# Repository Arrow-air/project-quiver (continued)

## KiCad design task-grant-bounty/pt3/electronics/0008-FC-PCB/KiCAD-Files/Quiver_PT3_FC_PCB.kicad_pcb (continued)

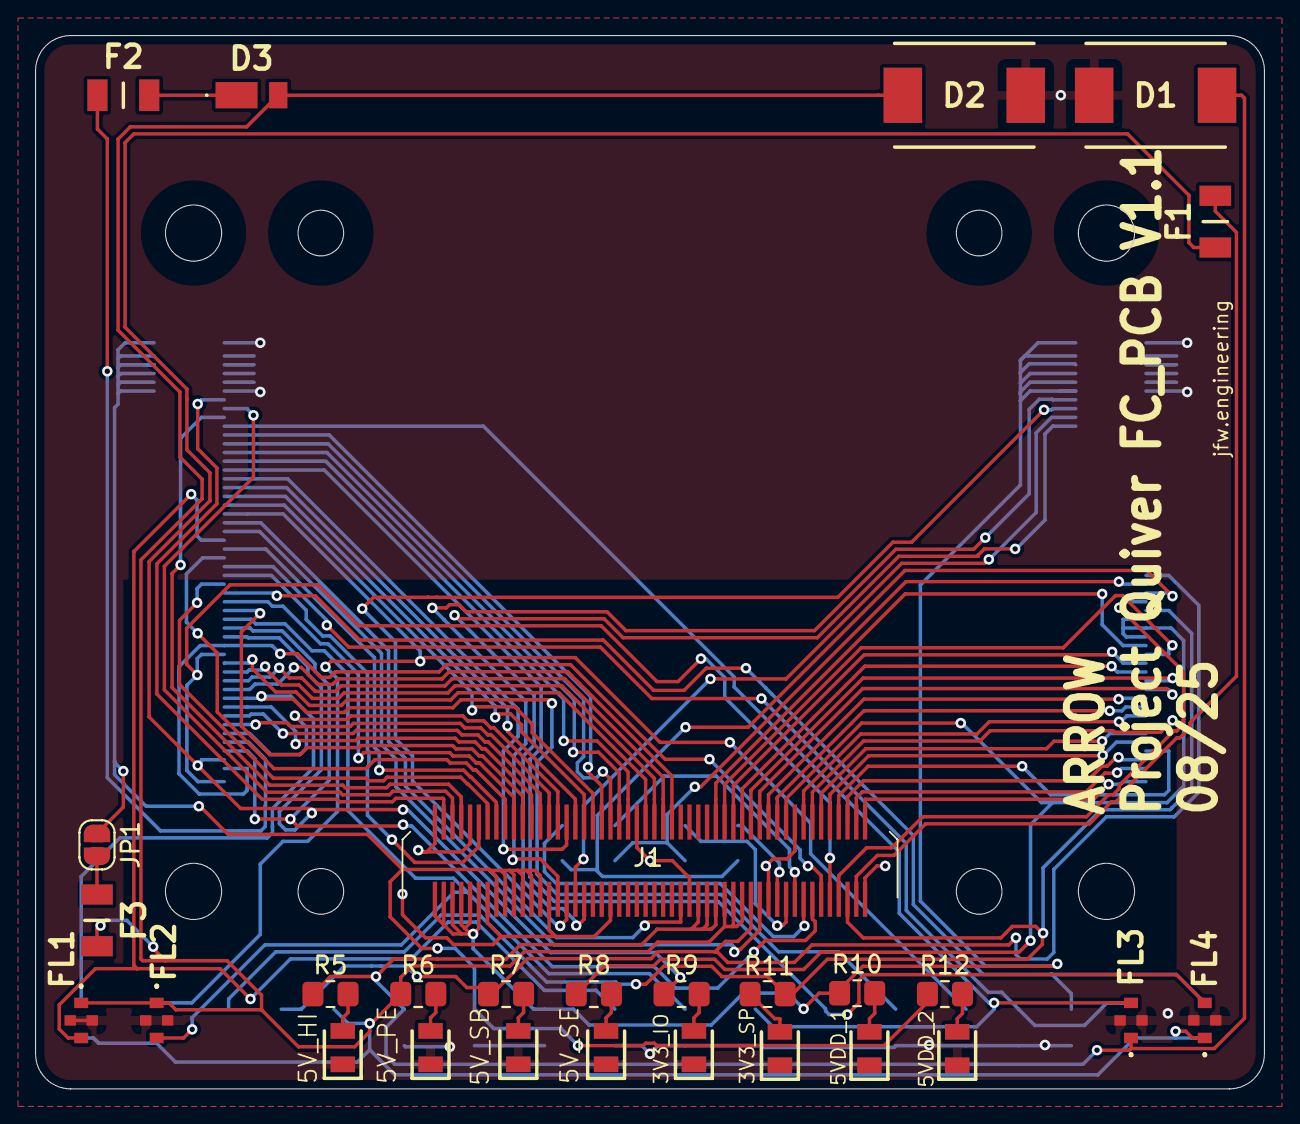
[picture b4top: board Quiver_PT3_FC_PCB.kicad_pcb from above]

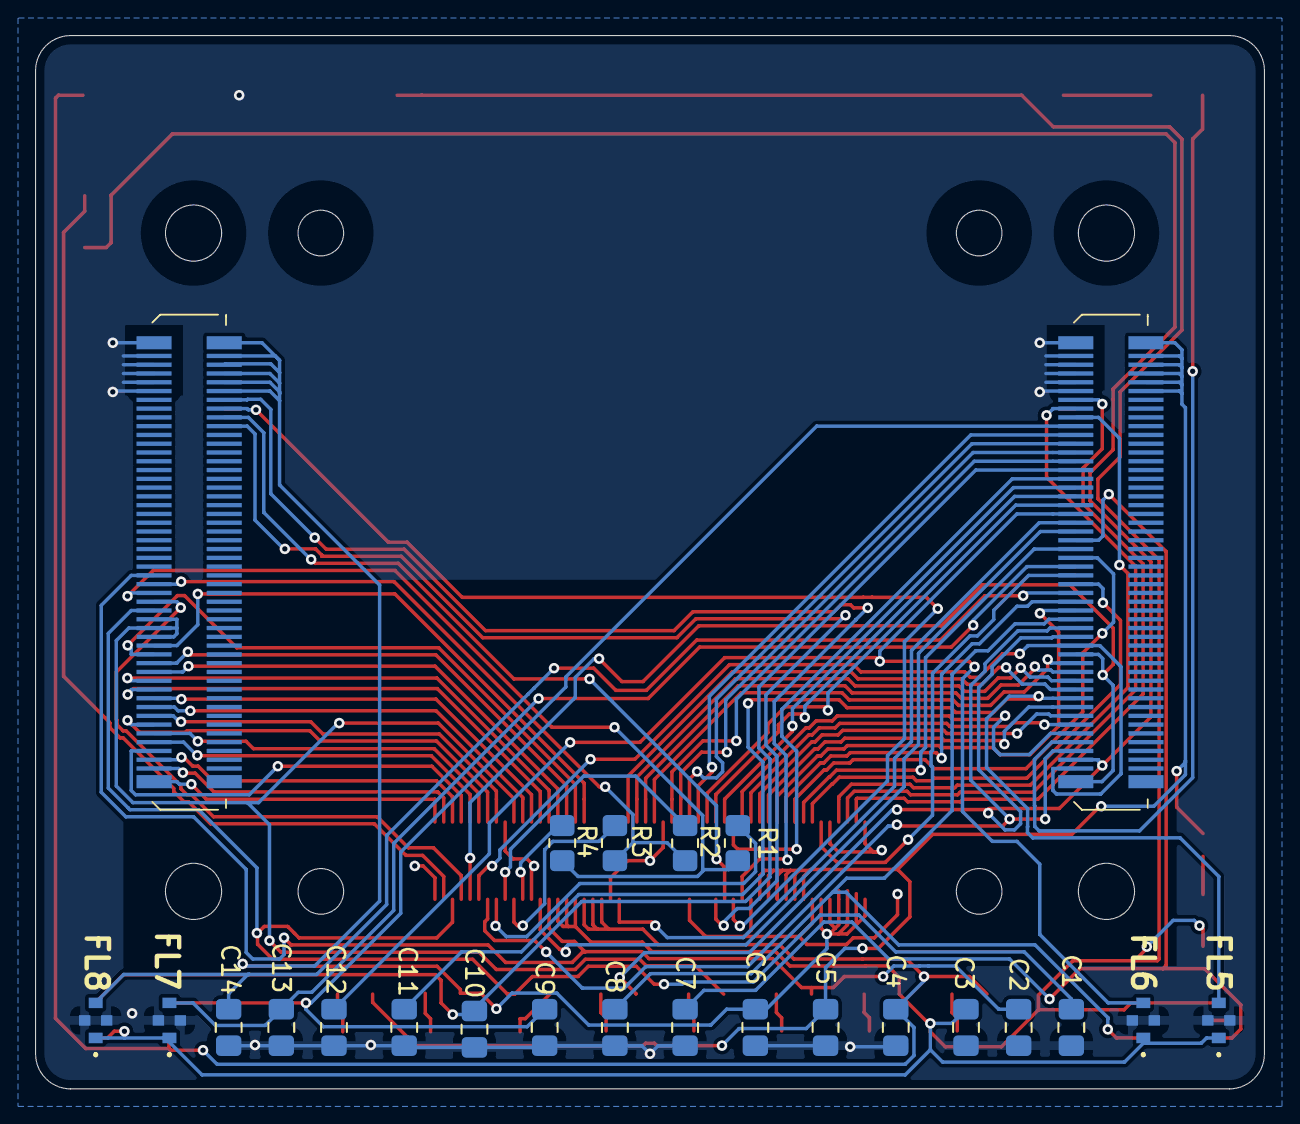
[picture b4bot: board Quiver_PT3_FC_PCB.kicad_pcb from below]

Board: 4 copper layers, 70.0 x 60.0 mm, 52 parts (24 on the bottom side), 86 nets.

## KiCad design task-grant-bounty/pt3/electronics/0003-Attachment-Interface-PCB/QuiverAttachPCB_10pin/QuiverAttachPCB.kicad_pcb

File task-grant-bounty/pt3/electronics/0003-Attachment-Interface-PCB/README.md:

# Project Quiver Payload Attachment PCB

## Overview

The Project Quiver payload attachment PCB is a simple 2-layer board designed for quickly interfacing payloads with the main system. 
This board provides standardized connectivity and mounting options for various payload configurations.

## Design Features

- **2-layer PCB design** for cost-effective manufacturing
- **Dual 10-pin headers** for flexible connectivity options
- **4x M2 mounting holes** for secure mechanical attachment
- **Configurable gender orientation** - populate either male or female connectors as needed

## Hardware Specifications

### Connectors
- **2x 10-pin headers** (2.54mm pitch)
  - Header J3: Female/Flat receiver pin payload interface
  - Header J2: Male/pogo pin interface
  - **Population options:**
    - Install male headers for mating with female cables/boards
    - Install female headers for mating with male cables/boards
    - Populate only one header if single connection is sufficient

### Mechanical
- **Mounting:** 4x M2 threaded holes
- **Board dimensions:** 15.8mm height x 23.5mm width
- **Board thickness:** 1.2mm **(thinner than standard 1,6mm!)**
- **Material:** FR4

## Assembly Instructions

### Component Population

1. **Header Selection:**
   - Determine required mating configuration
   - Install either male or female 10-pin headers (or both if needed)
   - Ensure proper alignment and orientation

2. **Mounting:**
   - Use 4x M2 screws for mechanical attachment
   - Recommended torque: screwdriver tightening, do not use impact driver or drill
   - Ensure even mounting pressure across all four points

### Pinout

**10-Pin Headers (J2 & J3):**

| Pin | J3 Function | J2 Function |
|-----|-------------|-------------|
| 1   | ETH_RX+    | ETH_RX+    |
| 2   | 12VSW      | 12VSW      |
| 3   | ETH_RX-    | ETH_RX-    |
| 4   | GND        | GND        |
| 5   | ETH_TX+    | ETH_TX+    |
| 6   | +12V       | +12V       |
| 7   | ETH_TX-    | ETH_TX-    |
| 8   | FMU_CH1    | FMU_CH1    |
| 9   | CAN1_P     | CAN1_P     |
| 10  | CAN1_N     | CAN1_N     |

**12-Pin MOLEX Locking Connector (J1 - 2077601281):**

| Pin | Function   | Description |
|-----|------------|-------------|
| 1   | ETH_RX+    | Ethernet receive positive |
| 2   | 12VSW      | Switched 12V power |
| 3   | ETH_RX-    | Ethernet receive negative |
| 4   | 12VSW      | Switched 12V power |
| 5   | ETH_TX+    | Ethernet transmit positive |
| 6   | GND        | Ground reference |
| 7   | ETH_TX-    | Ethernet transmit negative |
| 8   | GND        | Ground reference |
| 9   | CAN1_N     | CAN bus negative |
| 10  | 12V        | Main 12V power supply |
| 11  | CAN1_P     | CAN bus positive |
| 12  | FMU_CH1    | Flight Management Unit Channel 1 |

**Signal Descriptions:**
- **ETH_RX+/ETH_RX-**: Ethernet receive differential pair
- **ETH_TX+/ETH_TX-**: Ethernet transmit differential pair  
- **12VSW**: Switched 12V power output
- **+12V**: Main 12V power supply
- **GND**: Ground reference
- **FMU_CH1**: Flight Management Unit Channel 1
- **CAN1_P/CAN1_N**: CAN bus differential pair
s for maximum flexibility. J1 provides the same signals with additional ground pins for enhanced signal integrity and current handling.*
*Note: J2 and J3 headers have identical pinout

## Usage

### Configuration Options

1. **Single Header Configuration:**
   - Populate only J1 or J2 as needed
   - Use for simple payload interfaces

2. **Dual Header Configuration:**
   - Populate both headers
   - Enables 2x pin connections for each pinout

### Installation

1. Select appropriate M2 screws for your mounting surface
2. Align PCB with mounting holes
3. Secure with 4x M2 screws
4. Connect payload cables to populated headers

## Design Files

- Schematic: `QuiverAttachPCB.kicad_sch`
- PCB Layout: `QuiverAttachPCB.kicad_pcb`
- Gerber files: `/gerbers/`
- BOM: `QuiverAttachPCB_BOM.csv`

## Revision History

| Version | Date | Changes |
|---------|------|---------|
| v1.0    | 2025-06-02 | Initial release |
| v1.2    | 2025-07-31 | Center Molex header, adjust edge dimensions |

## Support

For technical questions or issues, please contact kellan@arrowair.com.

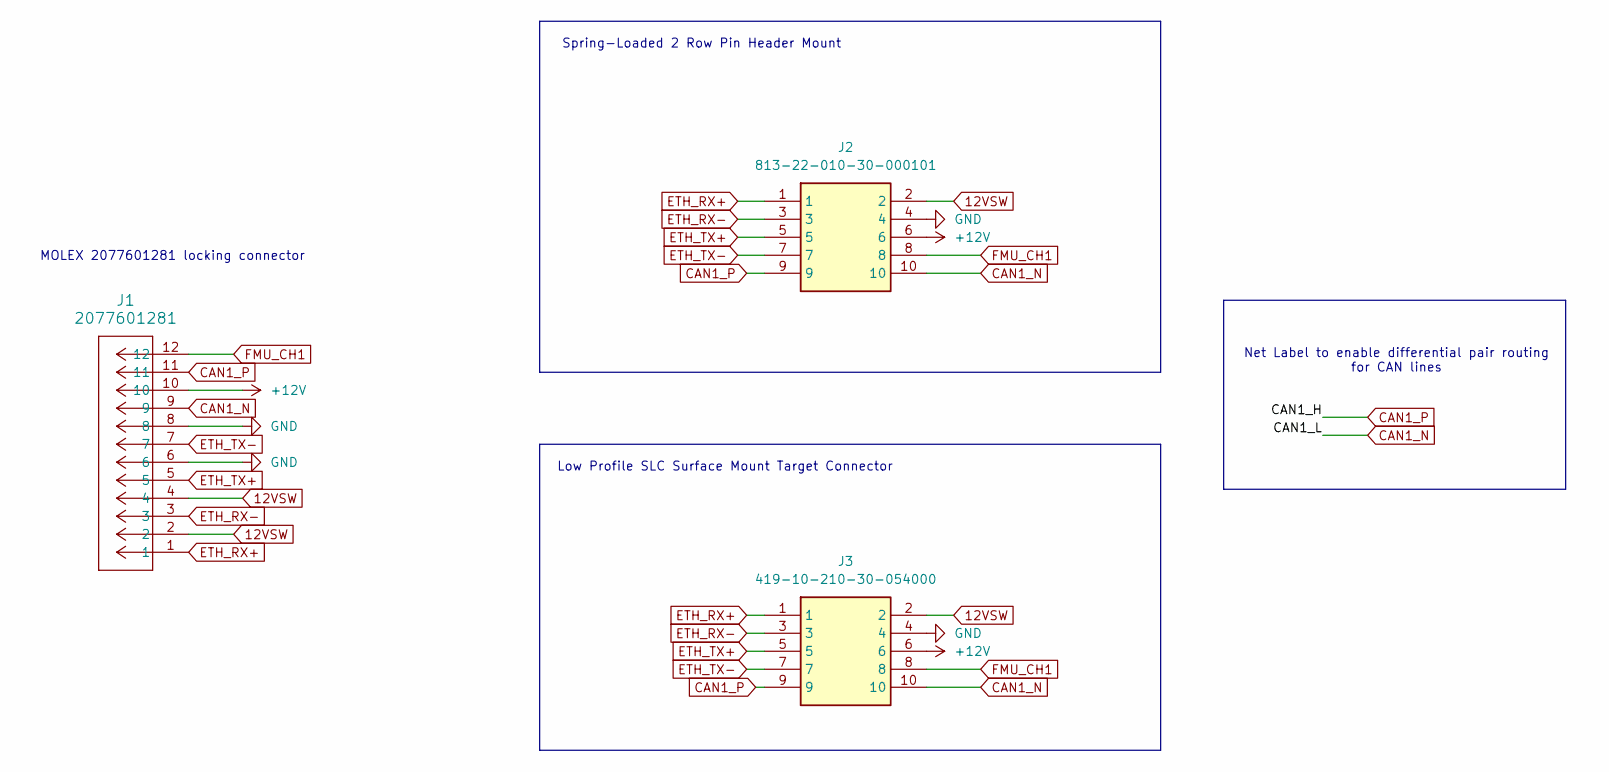
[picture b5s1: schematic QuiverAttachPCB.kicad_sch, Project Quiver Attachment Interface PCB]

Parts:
J1: 2077601281; CONN12_2077601281_MOL
J2: 813-22-010-30-000101; 8132201030000101; Mouser Part Number 575-8132201030000101
J3: 419-10-210-30-054000; Mouser Part Number 575-8132201030000101

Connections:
12VSW: J1.2, J1.4, J2.2, J3.2
+12V: J1.10, J2.6, J3.6
CAN1_N: J1.9, J2.10, J3.10
CAN1_P: J1.11, J2.9, J3.9
ETH_RX+: J1.1, J2.1, J3.1
ETH_RX-: J1.3, J2.3, J3.3
ETH_TX+: J1.5, J2.5, J3.5
ETH_TX-: J1.7, J2.7, J3.7
FMU_CH1: J1.12, J2.8, J3.8
GND: J1.6, J1.8, J2.4, J3.4

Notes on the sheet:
MOLEX 2077601281 locking connector
Spring-Loaded 2 Row Pin Header Mount
Low Profile SLC Surface Mount Target Connector
Net Label to enable differential pair routing for CAN lines

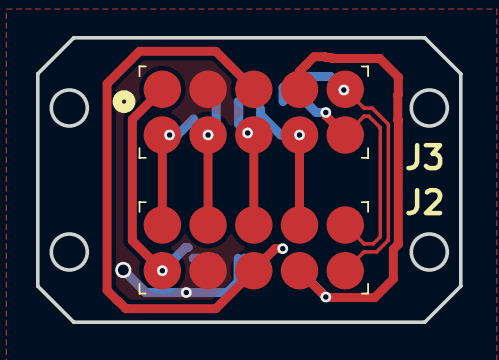
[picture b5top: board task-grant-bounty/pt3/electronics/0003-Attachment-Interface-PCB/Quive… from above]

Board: 2 copper layers, 23.5 x 15.8 mm, 3 parts (1 on the bottom side), 10 nets.

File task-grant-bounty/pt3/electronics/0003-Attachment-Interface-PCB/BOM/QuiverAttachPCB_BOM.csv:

QuiverAttachPCB
Id,Designator,Footprint,Quantity,Designation,Supplier,MPN,Product URL
1,J2,8132201030000101,1,813-22-010-30-000101,Mill-Max,813-22-010-30-000101,https://www.mouser.com/ProductDetail/Mill-Max/813-22-010-30-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
2,J1,CONN12_2077601281_MOL,1,2077601281,Molex,2077601281,https://www.mouser.com/ProductDetail/Molex/207760-1281?qs=Ge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
3,J3,419-10-210-30-054000,1,419-10-210-30-054000,Mill-Max,419-10-210-30-054000,https://www.mouser.com/ProductDetail/Mill-Max/419-10-210-30-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
,Not Populated,204523-1201,1,204523-1201,Molex,204523-1201,https://www.mouser.com/ProductDetail/Molex/204523-1201?qs=Ge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

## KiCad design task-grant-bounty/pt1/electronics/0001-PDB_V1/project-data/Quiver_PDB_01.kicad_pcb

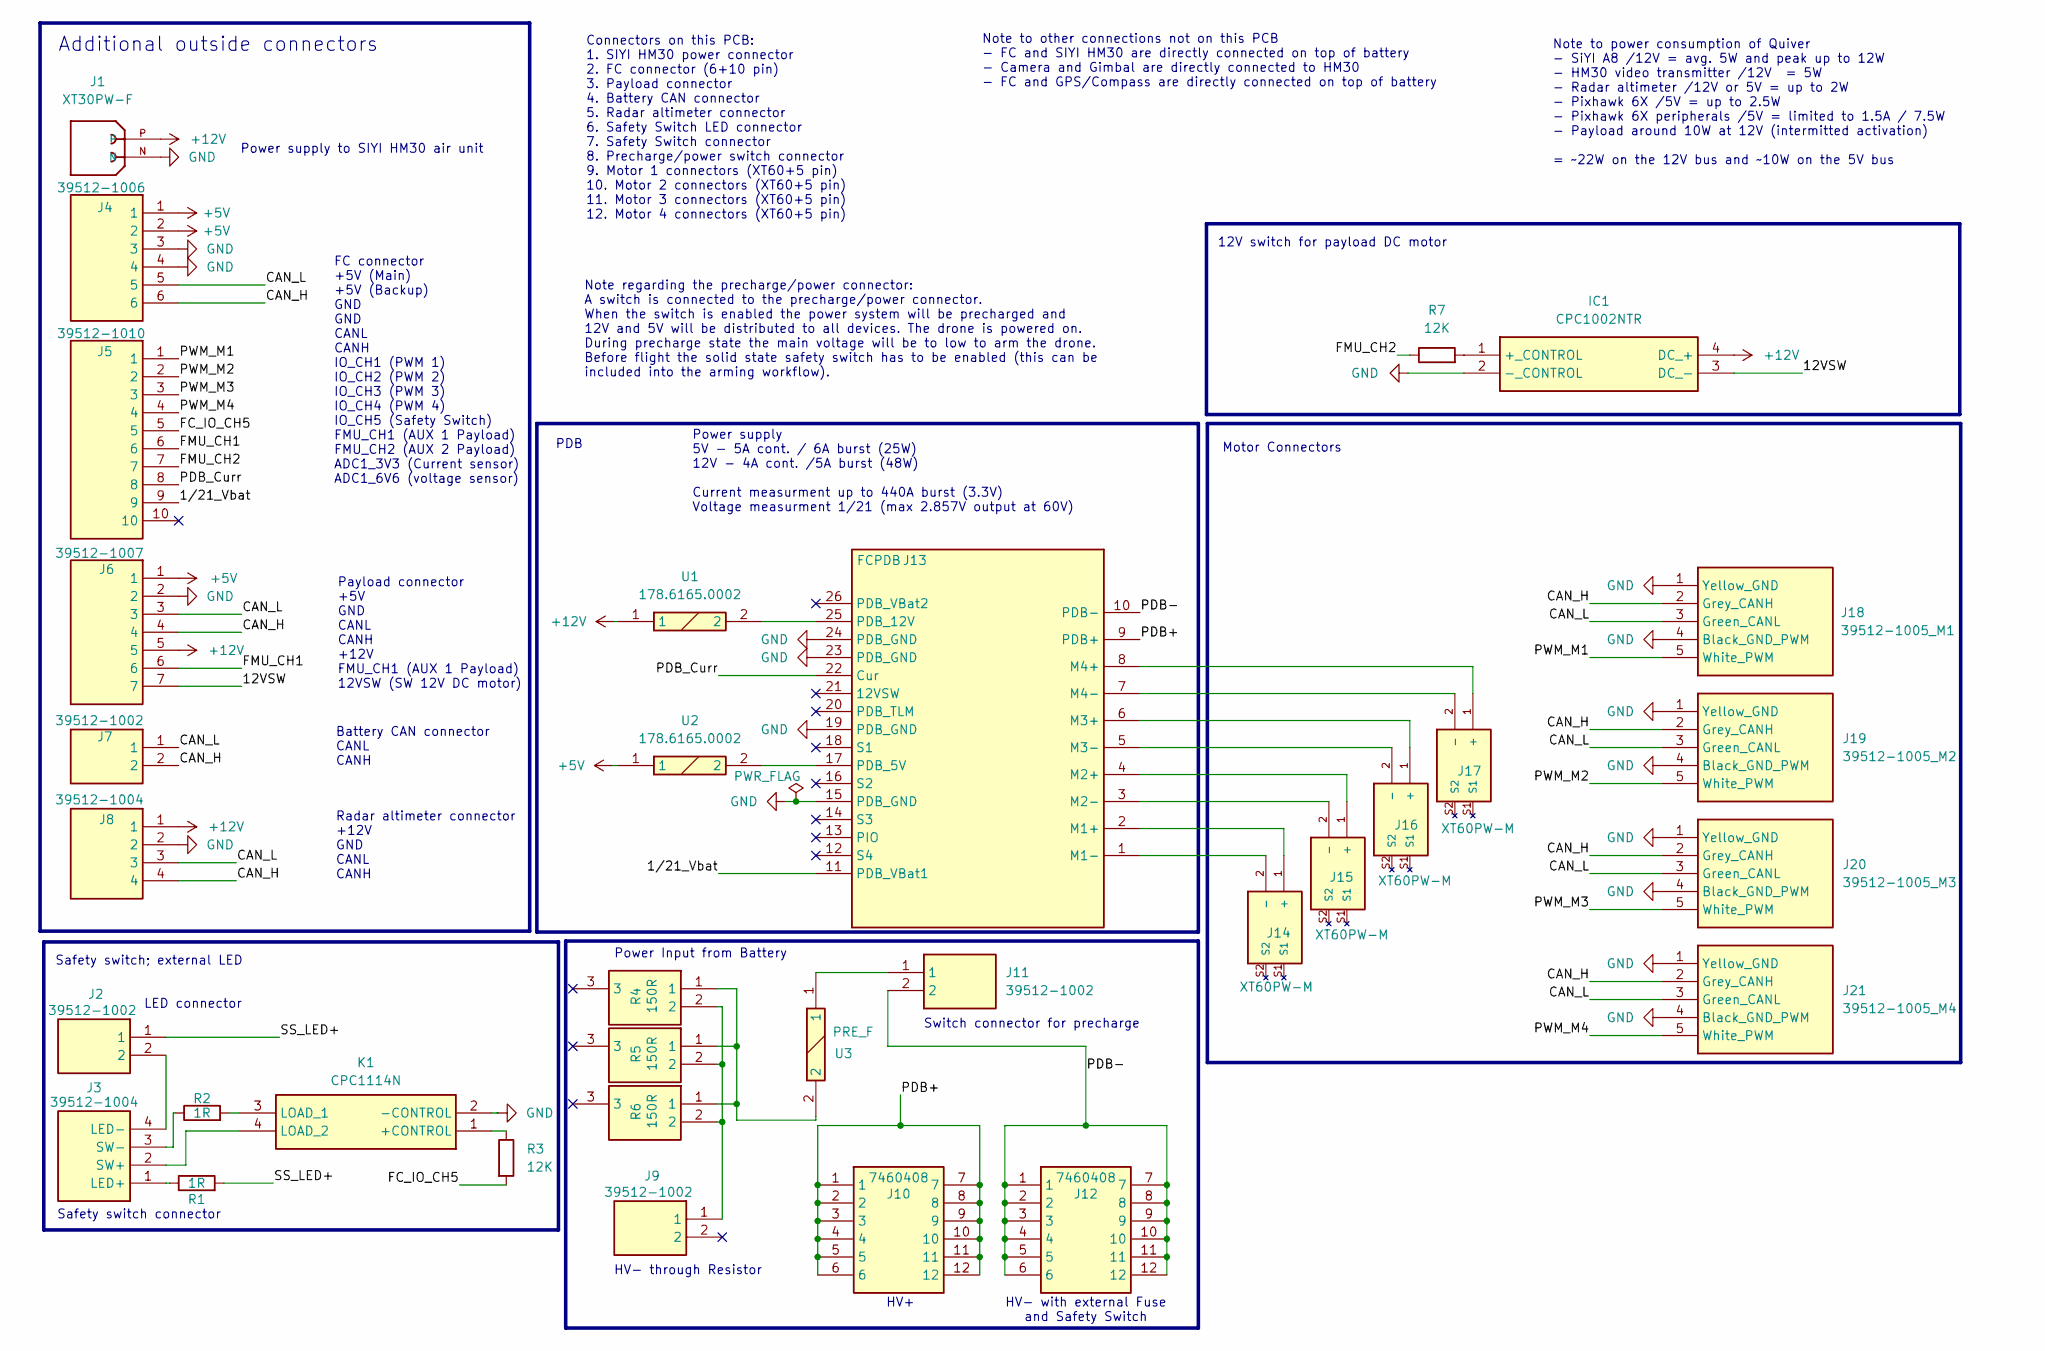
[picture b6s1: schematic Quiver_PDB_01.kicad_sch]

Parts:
IC1: CPC1002NTR; SOP254P610X216-4N; Mouser Part Number 849-CPC1002NTR
J1: XT30PW-F; XT30PW-F_AMASS_XT30PW-F; PARTREV 1.2
J2, J7, J9, J11: 39512-1002; SHDRRA2W80P0X381_1X2_901X920X730P; Mouser Part Number 538-39512-1002
J3, J8: 39512-1004; SHDRRA4W80P0X381_1X4_1663X920X730P; Mouser Part Number 538-39512-1004
J4: 39512-1006; 395121006; Mouser Part Number 538-39512-1005
J5: 39512-1010; 395121010; Mouser Part Number 538-39512-1005
J6: 39512-1007; 395121007; Mouser Part Number 538-39512-1005
J10, J12: 7460408; Mouser Part Number 710-7460408
J13: FCPDB; PDB_2; Mouser Part Number 200-SSQ12001FD
J14, J15, J16, J17: XT60PW-M; XT60PW-M_AMASS_XT60PW-M; PARTREV V1.2
J18: 39512-1005_M1; 395121005; Mouser Part Number 538-39512-1005
J19: 39512-1005_M2; 395121005; Mouser Part Number 538-39512-1005
J20: 39512-1005_M3; 395121005; Mouser Part Number 538-39512-1005
J21: 39512-1005_M4; 395121005; Mouser Part Number 538-39512-1005
K1: CPC1114N; SOP254P610X218-4N; Mouser Part Number 849-CPC1114N
R1, R2: 1R; R_0805_2012Metric_Pad1.20x1.40mm_HandSolder
R3, R7: 12K; R_0805_2012Metric_Pad1.20x1.40mm_HandSolder
R4, R5, R6: 150R; PWR163S2550R0F; Mouser Part Number 652-PWR163S-25-50R0F
U1, U2: 178.6165.0002; 17861650002; Mouser Part Number 576-178.6165.0002
U3: PRE_F; 17861650002; Mouser Part Number 576-178.6165.0002

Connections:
+5V: J4.1, J4.2, J6.1, U2.1
+12V: IC1.4 (DC_+), J1.P, J6.5, J8.1, U1.1
/1/21_Vbat: J5.9, J13.11 (PDB_VBat1)
/12VSW: IC1.3 (DC_-), J6.7
/CAN_H: J4.6, J6.4, J7.2, J8.4, J18.2 (Grey_CANH), J19.2 (Grey_CANH), J20.2 (Grey_CANH), J21.2 (Grey_CANH)
/CAN_L: J4.5, J6.3, J7.1, J8.3, J18.3 (Green_CANL), J19.3 (Green_CANL), J20.3 (Green_CANL), J21.3 (Green_CANL)
/FC_IO_CH5: J5.5, R3.2
/FMU_CH1: J5.6, J6.6
/FMU_CH2: J5.7, R7.1
/PDB+: J10.1, J10.2, J10.3, J10.4, J10.5, J10.6, J10.7, J10.8, J10.9, J10.10, J10.11, J10.12, J13.9 (PDB+)
/PDB-: J11.2, J12.1, J12.2, J12.3, J12.4, J12.5, J12.6, J12.7, J12.8, J12.9, J12.10, J12.11, J12.12, J13.10 (PDB-)
/PDB_Curr: J5.8, J13.22 (Cur)
/PWM_M1: J5.1, J18.5 (White_PWM)
/PWM_M2: J5.2, J19.5 (White_PWM)
/PWM_M3: J5.3, J20.5 (White_PWM)
/PWM_M4: J5.4, J21.5 (White_PWM)
/SS_LED+: J2.1, R1.2
GND: IC1.2 (-_CONTROL), J1.N, J4.3, J4.4, J6.2, J8.2, J13.15 (PDB_GND), J13.19 (PDB_GND), J13.23 (PDB_GND), J13.24 (PDB_GND), J18.1 (Yellow_GND), J18.4 (Black_GND_PWM), J19.1 (Yellow_GND), J19.4 (Black_GND_PWM), J20.1 (Yellow_GND), J20.4 (Black_GND_PWM), J21.1 (Yellow_GND), J21.4 (Black_GND_PWM), K1.2 (-CONTROL)
unnamed: IC1.1 (+_CONTROL), R7.2
unnamed: J3.1 (LED+), R1.1
unnamed: J2.2, J3.4 (LED-)
unnamed: J3.2 (SW+), K1.4 (LOAD_2)
unnamed: J3.3 (SW-), R2.1
unnamed: J9.1, R4.2, R5.2, R6.2
unnamed: J11.1, U3.1
unnamed: J13.2 (M1+), J14.1 (+)
unnamed: J13.1 (M1-), J14.2 (-)
unnamed: J13.4 (M2+), J15.1 (+)
unnamed: J13.3 (M2-), J15.2 (-)
unnamed: J13.6 (M3+), J16.1 (+)
unnamed: J13.5 (M3-), J16.2 (-)
unnamed: J13.8 (M4+), J17.1 (+)
unnamed: J13.7 (M4-), J17.2 (-)
unnamed: J13.17 (PDB_5V), U2.2
unnamed: J13.25 (PDB_12V), U1.2
unnamed: K1.1 (+CONTROL), R3.1
unnamed: K1.3 (LOAD_1), R2.2
unnamed: R4.1, R5.1, R6.1, U3.2

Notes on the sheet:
HV- with external Fuse and Safety Switch
HV+
HV- through Resistor
FC connector +5V (Main) +5V (Backup) GND GND CANL CANH IO_CH1 (PWM 1) IO_CH2 (PWM 2) IO_CH3 (PWM 3) IO_CH4 (PWM 4) IO_CH5 (Safety Switch) FMU_CH1 (AUX 1 Payload) FMU_CH2 (AUX 2 Payload) ADC1_3V3 (Current sensor) ADC1_6V6 (voltage sensor)
PDB
12V switch for payload DC motor
Power supply 5V - 5A cont. / 6A burst (25W) 12V - 4A cont. /5A burst (48W) Current measurment up to 440A burst (3.3V) Voltage measurment 1/21 (max 2.857V output at 60V)
Radar altimeter connector +12V GND CANL CANH
Power supply to SIYI HM30 air unit
Power Input from Battery
Motor Connectors
Switch connector for precharge
Battery CAN connector CANL CANH
Additional outside connectors
LED connector
Safety switch connector
Safety switch; external LED
Note to other connections not on this PCB - FC and SIYI HM30 are directly connected on top of battery - Camera and Gimbal are directly connected to HM30 - FC and GPS/Compass are directly connected on top of battery
Connectors on this PCB: 1. SIYI HM30 power connector 2. FC connector (6+10 pin) 3. Payload connector 4. Battery CAN connector 5. Radar altimeter connector 6. Safety Switch LED connector 7. Safety Switch connector 8. Precharge/power switch connector 9. Motor 1 connectors (XT60+5 pin) 10. Motor 2 con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
Note regarding the precharge/power connector: A switch is connected to the precharge/power connector. When the switch is enabled the power system will be precharged and 12V and 5V will be distributed to all devices. The drone is powered on. During precharge state the main voltage will be to low to 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
Note to power consumption of Quiver - SiYI A8 /12V = avg. 5W and peak up to 12W - HM30 video transmitter /12V = 5W - Radar altimeter /12V or 5V = up to 2W - Pixhawk 6X /5V = up to 2.5W - Pixhawk 6X peripherals /5V = limited to 1.5A / 7.5W - Payload around 10W at 12V (intermitted activation) = ~22W 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
Payload connector +5V GND CANL CANH +12V FMU_CH1 (AUX 1 Payload) 12VSW (SW 12V DC motor)

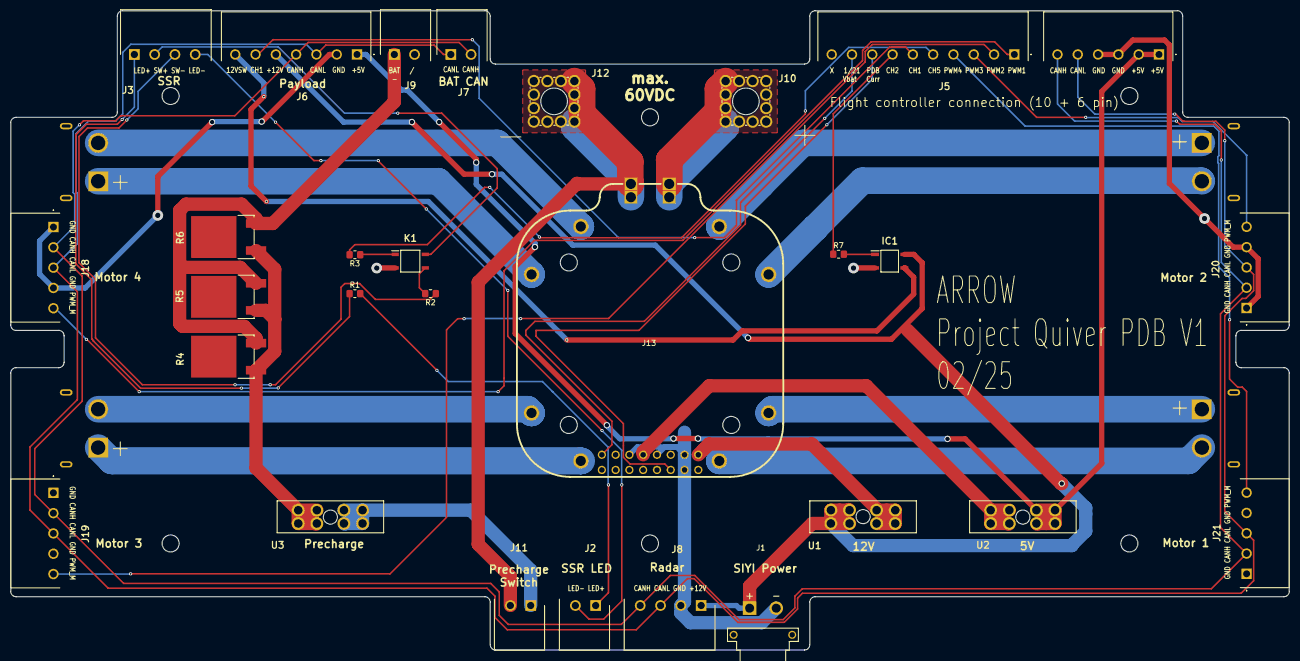
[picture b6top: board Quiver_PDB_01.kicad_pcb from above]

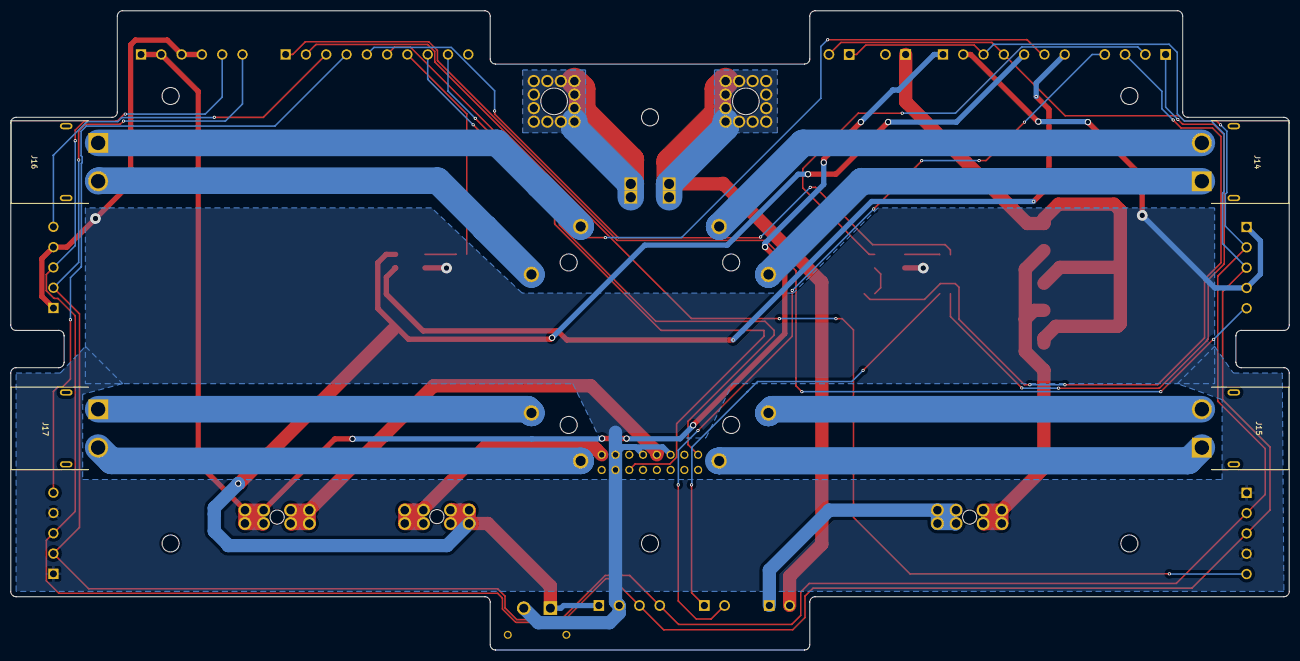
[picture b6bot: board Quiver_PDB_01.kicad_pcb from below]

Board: 2 copper layers, 240.0 x 120.0 mm, 33 parts (4 on the bottom side), 38 nets.

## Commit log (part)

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2026-02-25 adjusted folder structure
2026-02-25 information note format
2026-02-25 replacement log
2026-02-25 image folder
2026-02-25 placeholders
2026-02-26 docs: add nail board diagrams for all 28 harnesses (HAR-001 through HAR-028)
    - Add flat nail board PNGs for all harnesses with connector designators,
    pin assignments, wire colors/gauges, and BOM-derived cut lengths
    - Replace all [Image Placeholder] tags in Harness-Manufacturing-Guide.md
    - Grouped sections (HAR-004-007, HAR-008-011, HAR-012-013, HAR-019-020,
    HAR-021-022, HAR-023-025) show individual nail boards for each harness
    Generated by Vector from 4020_dev_kit.step geometry + harnessing guide data.
2026-02-26 docs: add cut lengths to Section 3 tables for all harnesses
    - HAR-0017: replace xxmm placeholder with 485 mm (BOM-derived)
    - HAR-0016: replace N/A with required cable length table (195 mm)
    - HAR-0019/020: replace N/A with JST-GH required lengths (170/160 mm)
    - HAR-0021/022: replace N/A with JST-GH required lengths (205/70 mm)
    - HAR-0023/024/025: replace N/A with JST-GH required lengths (120/205/155 mm)
    - HAR-0026: replace N/A with JST-GH required length (65 mm)
2026-02-26 Vector's update
2026-02-26 notation updated
2026-02-27 docs: Add OpenDroneID support (DroneBeacon db201) + updated firmware
    - arducopter-pixhawk6c.apj: rebuilt with AP_OPENDRONEID_ENABLED=1 (1,617 KB, 302 KB headroom)
    Standard Pixhawk 6C bootloader unchanged — firmware can still be updated freely.
    - parameters/params-remoteid.param: minimal param set to enable db201 via DroneCAN
    (DID_ENABLE, DID_CANDRIVER=1, DID_MAVPORT=-1)
    - docs/firmware/README.md: updated to document OpenDroneID support and param load order
2026-02-27 fix: Correct .apj firmware image encoding (zlib+base64, not raw base64)
    The previously generated .apj used raw base64-encoded binary, but ArduPilot's
    uploader expects zlib-compressed then base64-encoded image data. This caused
    Mission Planner to report 'Firmware file has 0 length image' when flashing.
    Fixed: compress with zlib.compress() before base64 encoding.
2026-03-03 feat: Add improved Tattu BMS DroneCAN bridge
    Fixes spurious SOC=0% readings with three changes:
    1. Drain full frame burst before DroneCAN spin:
    Original processed one frame per loop iteration, causing frame drops
    when the Tattu burst arrived faster than the loop ran.
    2. SOC/voltage sanity validation:
    Rejects out-of-range decodes (voltage outside 14S bounds, SOC > 100%)
2026-03-03 fix: Relax frame length validation — final Tattu frame is 6 bytes
    Frame 7 (the last frame) legitimately contains only 6 bytes in the Tattu
    protocol. The strict 'all frames >= 7 bytes' check was discarding every
    sequence. Now only frame 0 has a hard minimum; all other frames use
    min(len, 7) for reassembly.
2026-03-03 fix: db201 goes on CAN2, not CAN1 — CAN1 saturated by ESCs
    CAN1 is too busy with ESC traffic for db201 node ID enumeration to succeed.
    CAN2 at 1Mbps works reliably. Updated:
    - DID_CANDRIVER: 1 → 2
    - CAN_P2_BITRATE: set to 1000000 (overrides standard-params 500kbps)
2026-03-03 fix: db201 on CAN2 at 500kbps (shared with nanoradar)
    Remove CAN_P2_BITRATE override — CAN2 must stay at 500kbps for nanoradar.
    db201 CAN bitrate must be changed to 500kbps via DroneBeacon Bluetooth app
    before it will enumerate on CAN2.
2026-03-10 Rename task-grant-bounty/Dev-Kit/images/Quiver Payload Network.png to task-grant-bounty/Dev-Kit/images/payload/Quiver Payload Network.png
2026-03-10 Remove upload date from developer guide
    Removed upload date from the Quiver SDK Developer Guide.
2026-03-10 FIX formatting errors in last commit
2026-03-10 FIX folder error + UPDATE title for previous commit
2026-03-11 Hub/SDK Updates
2026-03-11 Enclosure Updates
2026-03-11 FIX format for previous commit
2026-03-11 Adjust Link and pictures
2026-03-11 jpg JPG
2026-03-11 Update vibration mount and weight reduction information noteand
2026-03-12 colon
2026-03-12 spacing
2026-03-18 hi alperen
2026-03-18 bye alperen
2026-03-23 Updated "warning" blockquote
2026-03-23 formatting and contnet updates
2026-03-23 Manufacturing guide updates
2026-03-23 PCB manuals added to Manufacturing guide
2026-03-23 Revise Quiver SDK Test information and references
    Updated revision history and reference notes for clarity.
2026-03-26 UPDATE pilot-handbook for "gimbal camera" + multiple "failure" + "contact" parts
2026-03-30 Update Pilot-Handbook.md
    Safety-Critical Gaps
    2. §3.3 Step 9 / §2.5.3 — Replace "adequate GPS fix" with a specific threshold.
2026-04-10 fix: db201 confirmed working on CAN1; update params from flight testing
    params-remoteid.param:
    - DID_CANDRIVER: 2 → 1 (CAN1 confirmed working with ESCs)
    - Added DID_BARO_ACC=-1
    - Removed CAN2/500kbps workaround notes
    standard-params.param:
    - GPS_HDOP_GOOD: 140 → 160
2026-04-14 docs: add Quiver PT1 bill of materials
    - Markdown page formatted for Docusaurus with categorized tables
    - CSV source file for programmatic access
    - Sourced from the PT1 BOM Google Sheet
    - Links to suppliers, specs, and quantities for all components
    - Cost summary: ~$6,970 per build
2026-04-15 Relocate structural assembly guide and assets
    Move General-Assembly-Guide contents up to Assembly-Guides and regroup assets under assets/images/structural and assets/models/structural. Update image and CAD references in structural-assembly.md.
2026-04-15 Update asset paths in structural assembly guide
    Point image and CAD links to assets/images/structural and assets/models/structural after the asset relocation.
2026-04-15 Revise Dev-Kit Engineering Report with updates
    Updated the Dev-Kit Engineering Report with new sections on structural improvements, electronics integration, software upgrades, and performance metrics. Adjusted sidebar position and added detailed 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
2026-04-15 Add missing step13_1 image for structural assembly guide
2026-04-15 fix: add missing images referenced by assembly and manufacturing docs
    - Copy step13_1.png to structural assembly assets (was only in pt3-assembly-guides)
    - Copy 1221_1222.png and .step to Dev-Kit-Guides/assets (Manufacturing-Guide references)
2026-04-15 fix: replace broken image refs with TODO placeholders
    Images differ between PT3 and devkit, so using PT3 assets would be
    incorrect. Replaced with TODO notes until correct devkit images are available.
    Affected files:
    - structural-assembly.md: step13_1.png (busbar installation)
    - Manufacturing-Guide.md: 1221_1222.png and .step (battery wall)
2026-04-16 Add transport case foam insert information note
    Add Pelican 1640 custom foam insert documentation for the Quiver
    transport case bounty (Issue #192). Includes:
    - Information note with foam layer design, CAD links, manufacturing
    process, material list, and assembly instructions
    - 5 reference images (2 CAD renders, 3 build photos)
    - 2 DXF laser cutting layouts (Foam_1.dxf, Foam_2.dxf)
2026-04-16 Update structural assembly guide (BOM, HTML images, step shift)
    - Move tool list into BOM as Table 3 (Tools and Consumables) with McMaster refs for Loctite 222/242 and Würth Super RTV Silicone
    - Remove silicone adhesive between aluminum layer references and delete the four contact images (step1_3, step2_3, step4_3, step5_3)
    - Convert all image references to HTML img tags with width="600"
    - Shift Steps 19-21 to Steps 20-22 and rename associated assets to free the Step 19 slot
    - Populate Step 20 (Main Enclosure and Top Cap) parts list including consumables
    - Replace step16_1.png with upscaled version
2026-04-17 Fix landing legs wording, remove bounty proposal section
    - Change 'minus detached landing legs' to 'with detached landing legs'
    - Remove Bounty or Grant Proposal Document section (no formal bounty
    proposal exists for this work)
2026-04-17 Revise structural assembly guide: fastener corrections, consumables, wording
    - Fix BOM quantities to match step usage across all fasteners
    - Remove unused Screw 3 (old) and Insert 3 (old), renumber Screw 18 and Insert 5 into the freed slots
    - Add consumables (Loctite, Würth RTV, double-sided tape, silicone foam seal strip) to Parts needed in all steps that use them
    - Normalize parenthetical fastener descriptions to match BOM exactly
    - Fix grammar: "shown to" -> "shown in", "connecters" -> "connectors", consistent "DO NOT use" casing
    - Fix Step 14 fastener type (Screw 5 vs Screw 7) and Step 13 missing Loctite in parts list
2026-04-18 fix: sync Manufacturing-Guide with structural-assembly v1.1 changes
    Alperen's PR #195 reorganized structural-assembly.md, removing the
    'Adhesive Area' column and consolidating steps to 2 images each.
    Manufacturing-Guide.md still had the old 3-column tables referencing
    deleted images (step1_3, step2_3, step4_3, step5_3, step9_6).
    Updated tables to match the current 2-column structure rather than
    leaving TODO placeholders.
2026-04-20 docs: sync BOM with Google Sheet updates
    - Add 134X: aluminum landing gear tube joints (INNLOI) replacing 3D-printed T-adapters
    - Add 3231: power switch (Digikey)
    - Update CF tube dimensions from 30x26 to 30x28mm
    - Update total estimate to ~$7,023
2026-04-20 docs: major BOM update from Alperen's manufacturing guide alignment
    - Remove old fastener section (0023-0040) — replaced by detailed 51XX series
    - Add all 3D-printed parts (21X1, 2131, 221X, 2311-2341, 2411-2412)
    - Add new equipment: PPP adapter (3271), busbars (3322/3323), power switch (3231)
    - Renumber: shock absorber → 135X, Remote ID → 3261
    - Add complete Misc section (5XXX): rivets, screws, inserts, washers, grommets, seals, vibration mounts, tools, adhesives
    - Update 133X supplier link to RJXHobby
2026-04-20 Update PPP Adapter part number in assembly guide
2026-04-20 docs: add hyperlinks to all McMaster P/Ns and Amazon items in Misc section
2026-04-20 docs: add exact Amazon links for misc hardware (5132-5135)
2026-04-21 Update step3_3 threadlocker application image
2026-04-21 Add Loctite Red 262 for motor arm connector fasteners
    - Add Loctite Threadlocker Red 262 (high-strength) to Tools and Consumables table with McMaster reference
    - Step 3: use Red 262 on the permanent motor arm connector fasteners; Blue 242 stays for the connector-to-chassis screws
    - Step 21: explicitly call out Loctite Purple 222 application for antennas (small amount on base threads) and push button
2026-04-21 Restructure General Assembly section with updated BOM and steps
2026-04-22 fix: Correct .apj magic string (APFWv1 → APJFWv1)
    Our hand-generated .apj used 'APFWv1' but ArduPilot's standard is 'APJFWv1'.
    The OTA service's apj→abin converter checks for this magic and would reject
    our custom .apj files.
2026-04-30 docs: update pilot handbook relay startup guidance
2026-04-30 ci: ignore generated hardware artifacts in sanity checks
2026-04-30 docs: add SSR verification fallback
2026-04-30 docs: clarify SSR verification without Tattu bridge
2026-04-30 Adding Archive folder to Guides
2026-05-01 docs: remove ADR and meeting templates
2026-05-05 Fix archived SDK guide image path
2026-05-06 docs: include updated devkit engineering report draft
2026-05-11 Reorder Screw 3 to correct numerical position in fasteners BOM
2026-05-12 docs: localize dev kit report images
2026-05-12 Update NRA15 and camera bolt sizes per assembly feedback
2026-05-13 docs: reorganize Quiver documentation IA
    Group current Quiver docs by audience and workflow, archive legacy PT3 assembly material, and clean up sidebar labels/order for the Docusaurus import.
2026-05-13 docs: update bottom payload harness instructions
2026-05-13 docs: add HAR-014 complete harness reference photo
2026-05-13 docs: fix HAR-014 reference photo rendering
2026-05-14 docs: dedupe manufacturing and harness guides
2026-05-15 docs: normalize harness IDs in tables
2026-05-15 docs: rename canonical Quiver BOM
2026-05-15 docs: sync BOM from Google Sheet
2026-05-20 docs: add PWM MAD 4x08 parameter variant
2026-05-29 Added fusion link to project readme and manufacturing guide
2026-06-10 Revert "fixup! ci: terraform provisioned file changes"
    This reverts commit 0f2abc5e3766a2f459a777524694517443e961b1.
2026-06-11 fix: restore repo-specific cspell ignore paths
    The June 7 Terraform repository sync overwrote this file with the
    shared org template, dropping the KiCad/hardware binary ignore paths
    added in #219. Terraform no longer manages this file's content
    (Arrow-air/tf-github#162), so this restore will stick.
2026-06-17 fix: rebuild Pixhawk6C firmware with RPLidar S2 support
